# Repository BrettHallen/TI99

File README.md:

# [PSU Replacement](/TI994A_PSU_Replacement)
A fork of a fork.  <br>
Created a version using KiCad 9, with rounded corners and more information to make the build more "idiot proof".<br>

Replaces the 99/4A's original dual-voltage 18VAC/7.5VAC power supply with a regulated 12VDC supply.  The board then generates the required ±5VDC voltages using a DC-DC buck converter (+5VDC) and switching regulator (-5VDC).  The +12VDC comes directly from the external power supply.<br>

## Main Parts
- DFRobot DFR0831 DC-DC Buck Converter (+5VDC supply)
- Recom R-78CK5.0-0.5 Switching Regulator (-5VDC supply)
- Vishay SUP53P06-20 MOSFET (protects against reverse polarity DC input)
- G-Switch SS-22G88-G090 DPDT switch (need to trim a little)

## Original Designs
- [Johnny Blanchard's original](https://codeberg.org/Jonn-reenthused/TI99-4A-dc-power-board)
- [dabone's fork](https://github.com/dabonetn/ti99psu-replacement)

## Status
- 2-Nov-2025: Designed, not yet fabbed & tested, need to double-check switch position

# [Joystick Adaptor](/JoystickAdaptor)
Wanted to design my own joystick adaptor, so I did.

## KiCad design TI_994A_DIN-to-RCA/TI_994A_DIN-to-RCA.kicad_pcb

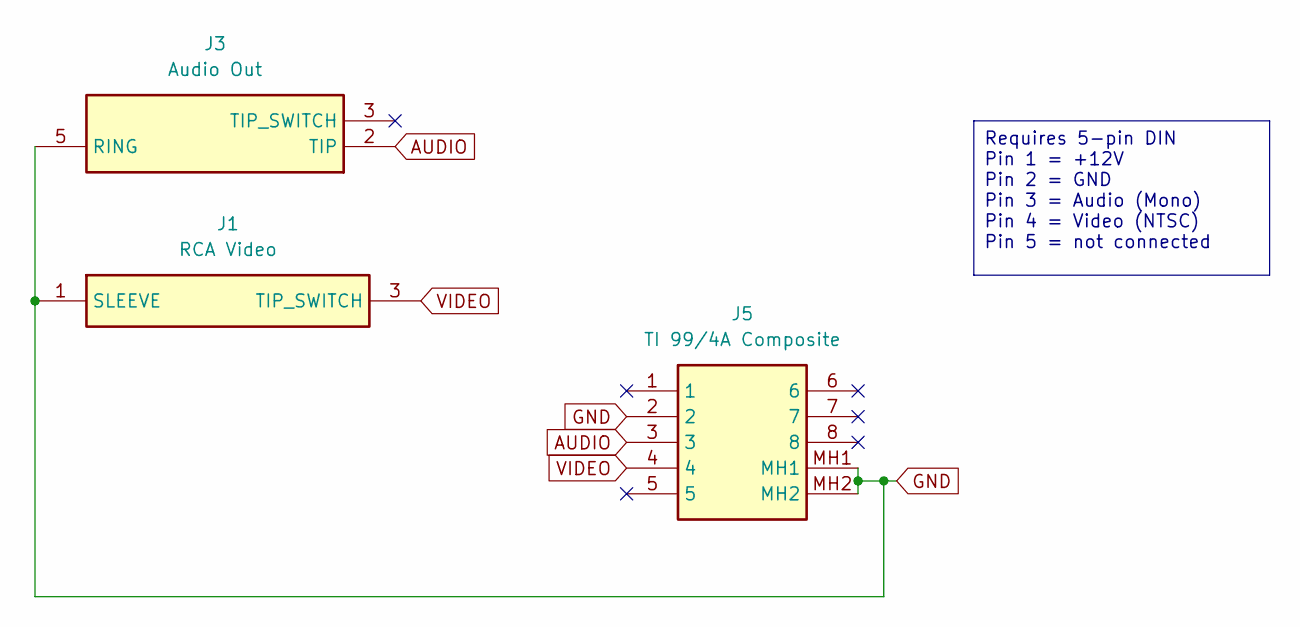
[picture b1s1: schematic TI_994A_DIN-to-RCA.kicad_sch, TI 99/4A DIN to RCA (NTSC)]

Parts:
J1: RCA Video; FC68371; Manufacturer_Part_Number FC68371
J3: Audio Out; SJ3350820BTR; Mouser Part Number 179-SJ3-350820B-TR
J5: TI 99/4A Composite; 6710801; Manufacturer_Part_Number 671-0801

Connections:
AUDIO: J3.2 (TIP), J5.3
GND: J1.1 (SLEEVE), J3.5 (RING), J5.2, J5.MH1, J5.MH2
VIDEO: J1.3 (TIP_SWITCH), J5.4

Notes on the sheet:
Requires 5-pin DIN Pin 1 = +12V Pin 2 = GND Pin 3 = Audio (Mono) Pin 4 = Video (NTSC) Pin 5 = not connected

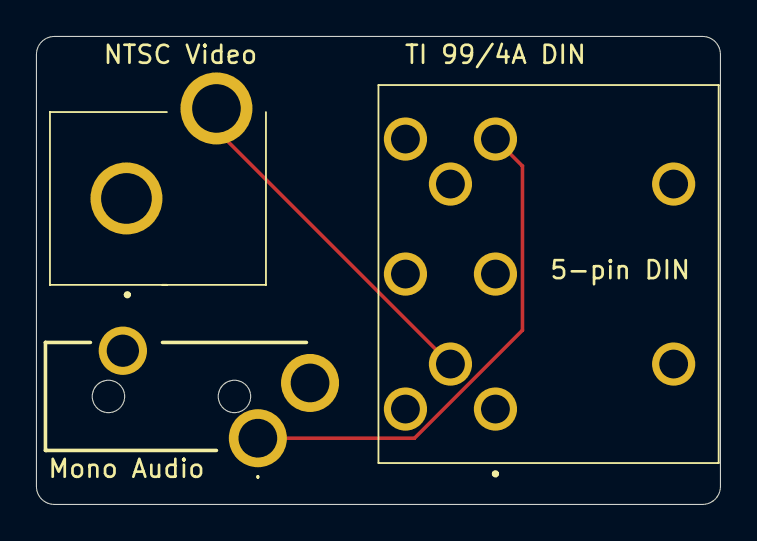
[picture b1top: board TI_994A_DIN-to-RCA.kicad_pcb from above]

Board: 2 copper layers, 38.0 x 26.0 mm, 3 parts (0 on the bottom side), 3 nets.

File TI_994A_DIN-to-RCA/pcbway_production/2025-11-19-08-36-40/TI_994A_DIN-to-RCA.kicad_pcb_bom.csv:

Designator,Quantity,Value,Footprint,Package,MPN,DNP,Mount_Type,Description,Height,Manufacturer_Name,Mouser Part Number,Mouser Price/Stock
J1,1,RCA Video,FC68371,,FC68371,,tht,Socket; RCA; female; angled 90; THT; nickel plated; Marker: black,14,CLIFF ELECTRONIC COMPONENTS,,
J3,1,Audio Out,SJ3350820BTR,,SJ3-350820B-TR,,tht,"3.5 mm Stereo Jack, Through Hole, 2 Conductors, 1 Internal Switches,  Tape & Reel Packaging",5.3,Same Sky,179-SJ3-350820B-TR,https://www.mouser.co.uk/ProductDetail/Same-Sky/SJ3-350820B-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
J5,1,TI 99/4A Composite,6710801,,671-0801,,tht,"Deltron 8 Pole Right Angle Din Socket Socket, 2A, 100 V ac, Lockable",19.5,DELTRON COMPONENTS,,

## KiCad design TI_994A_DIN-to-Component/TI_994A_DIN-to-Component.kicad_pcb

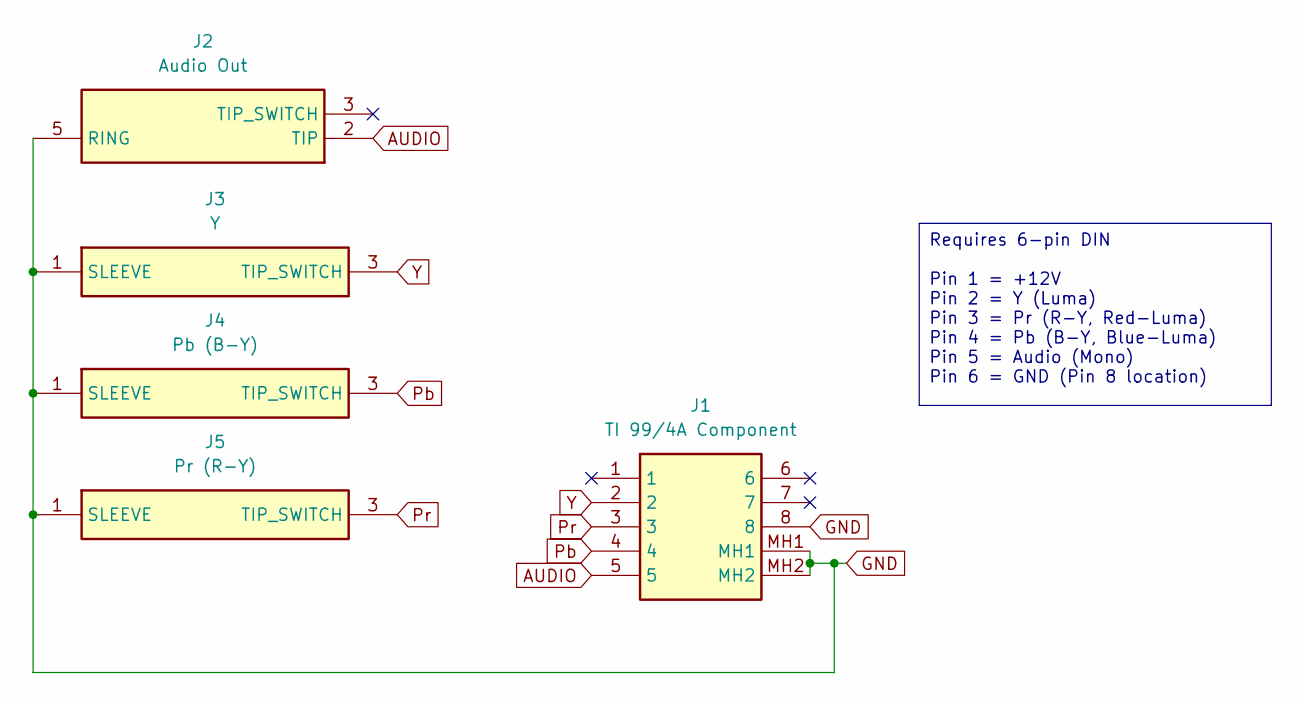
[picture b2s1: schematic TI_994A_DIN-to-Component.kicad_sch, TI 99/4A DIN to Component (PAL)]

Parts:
J1: TI 99/4A Component; 6710801; Manufacturer_Part_Number 671-0801
J2: Audio Out; SJ3350820BTR; Mouser Part Number 179-SJ3-350820B-TR
J3: Y; FC68371; Manufacturer_Part_Number FC68371
J4: Pb (B-Y); FC68371; Manufacturer_Part_Number FC68371
J5: Pr (R-Y); FC68371; Manufacturer_Part_Number FC68371

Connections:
AUDIO: J1.5, J2.2 (TIP)
GND: J1.8, J1.MH1, J1.MH2, J2.5 (RING), J3.1 (SLEEVE), J4.1 (SLEEVE), J5.1 (SLEEVE)
Pb: J1.4, J4.3 (TIP_SWITCH)
Pr: J1.3, J5.3 (TIP_SWITCH)
Y: J1.2, J3.3 (TIP_SWITCH)

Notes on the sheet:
Requires 6-pin DIN Pin 1 = +12V Pin 2 = Y (Luma) Pin 3 = Pr (R-Y, Red-Luma) Pin 4 = Pb (B-Y, Blue-Luma) Pin 5 = Audio (Mono) Pin 6 = GND (Pin 8 location)

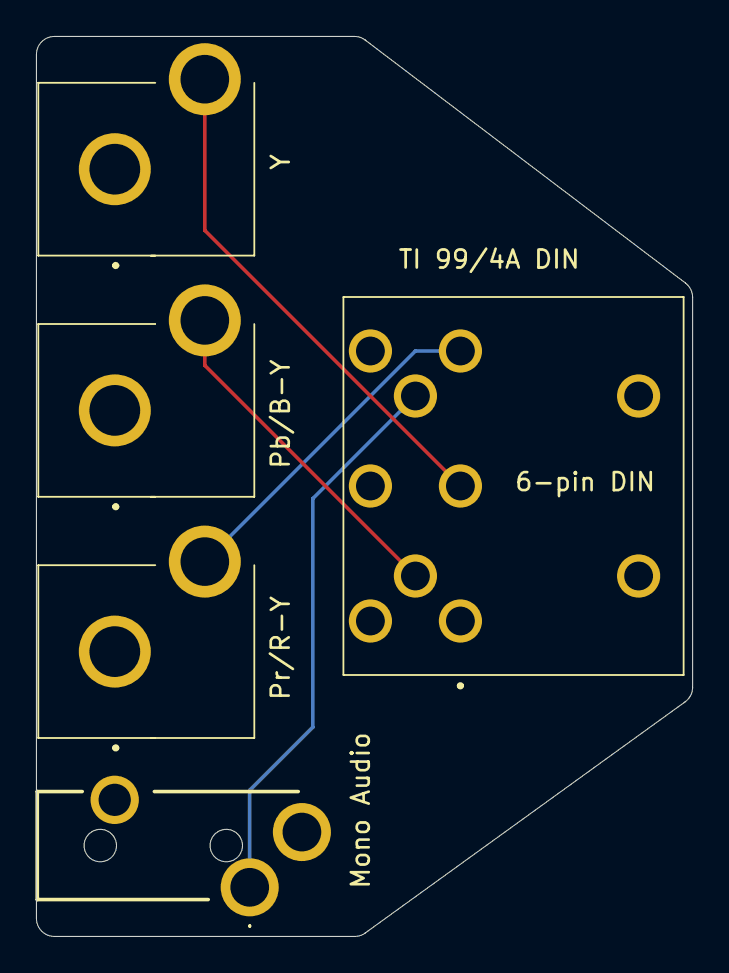
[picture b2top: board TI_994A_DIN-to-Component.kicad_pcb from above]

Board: 2 copper layers, 36.5 x 50.0 mm, 5 parts (0 on the bottom side), 5 nets.

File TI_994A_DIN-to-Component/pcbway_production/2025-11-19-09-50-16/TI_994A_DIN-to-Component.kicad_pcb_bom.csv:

Designator,Quantity,Value,Footprint,Package,MPN,DNP,Mount_Type,Description,Height,Manufacturer_Name,Mouser Part Number,Mouser Price/Stock
J1,1,TI 99/4A Component,6710801,,671-0801,,tht,"Deltron 8 Pole Right Angle Din Socket Socket, 2A, 100 V ac, Lockable",19.5,DELTRON COMPONENTS,,
J2,1,Audio Out,SJ3350820BTR,,SJ3-350820B-TR,,tht,"3.5 mm Stereo Jack, Through Hole, 2 Conductors, 1 Internal Switches,  Tape & Reel Packaging",5.3,Same Sky,179-SJ3-350820B-TR,https://www.mouser.co.uk/ProductDetail/Same-Sky/SJ3-350820B-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
J3,1,Y,FC68371,,FC68371,,tht,Socket; RCA; female; angled 90; THT; nickel plated; Marker: black,14,CLIFF ELECTRONIC COMPONENTS,,
J4,1,Pb (B-Y),FC68371,,FC68371,,tht,Socket; RCA; female; angled 90; THT; nickel plated; Marker: black,14,CLIFF ELECTRONIC COMPONENTS,,
J5,1,Pr (R-Y),FC68371,,FC68371,,tht,Socket; RCA; female; angled 90; THT; nickel plated; Marker: black,14,CLIFF ELECTRONIC COMPONENTS,,

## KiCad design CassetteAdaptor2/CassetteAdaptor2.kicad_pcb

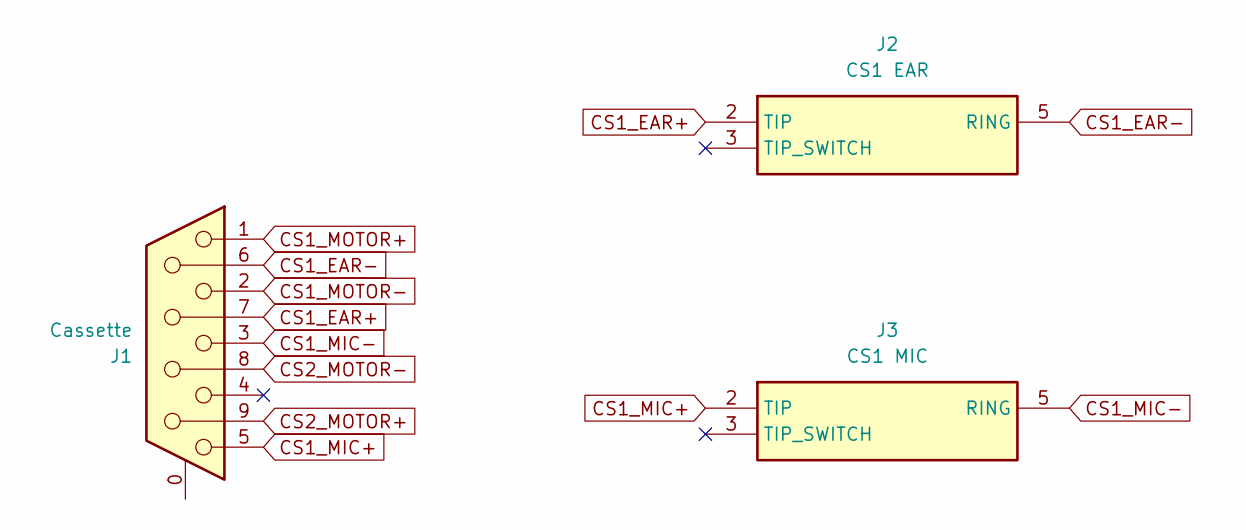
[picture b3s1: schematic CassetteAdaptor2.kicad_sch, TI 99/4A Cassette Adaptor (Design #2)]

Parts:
J1: Cassette; DSUB-9_Pins_EdgeMount_P2.77mm
J2: CS1 EAR; SJ3350820BTR; Mouser Part Number 179-SJ3-350820B-TR
J3: CS1 MIC; SJ3350820BTR; Mouser Part Number 179-SJ3-350820B-TR

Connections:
CS1_EAR+: J1.7, J2.2 (TIP)
CS1_EAR-: J1.6, J2.5 (RING)
CS1_MIC+: J1.5, J3.2 (TIP)
CS1_MIC-: J1.3, J3.5 (RING)
CS1_MOTOR+: J1.1
CS1_MOTOR-: J1.2
CS2_MOTOR+: J1.9
CS2_MOTOR-: J1.8

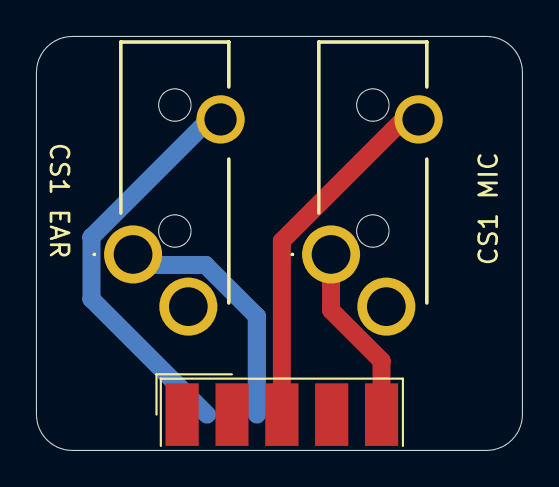
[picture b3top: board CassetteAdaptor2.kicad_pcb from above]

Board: 2 copper layers, 27.0 x 23.0 mm, 3 parts (0 on the bottom side), 4 nets.

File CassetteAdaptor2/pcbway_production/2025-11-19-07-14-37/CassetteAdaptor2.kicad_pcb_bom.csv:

Designator,Quantity,Value,Footprint,Package,MPN,DNP,Mount_Type,Description,Height,Mouser Part Number,Mouser Price/Stock,Manufacturer_Name
J1,1,Cassette,DSUB-9_Pins_EdgeMount_P2.77mm,,,,smt,"9-pin D-SUB connector, socket (female), Mounting Hole",,,,
J2,1,CS1 EAR,SJ3350820BTR,,SJ3-350820B-TR,,tht,"3.5 mm Stereo Jack, Through Hole, 2 Conductors, 1 Internal Switches,  Tape & Reel Packaging",5.3,179-SJ3-350820B-TR,https://www.mouser.co.uk/ProductDetail/Same-Sky/SJ3-350820B-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,Same Sky
J3,1,CS1 MIC,SJ3350820BTR,,SJ3-350820B-TR,,tht,"3.5 mm Stereo Jack, Through Hole, 2 Conductors, 1 Internal Switches,  Tape & Reel Packaging",5.3,179-SJ3-350820B-TR,https://www.mouser.co.uk/ProductDetail/Same-Sky/SJ3-350820B-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,Same Sky

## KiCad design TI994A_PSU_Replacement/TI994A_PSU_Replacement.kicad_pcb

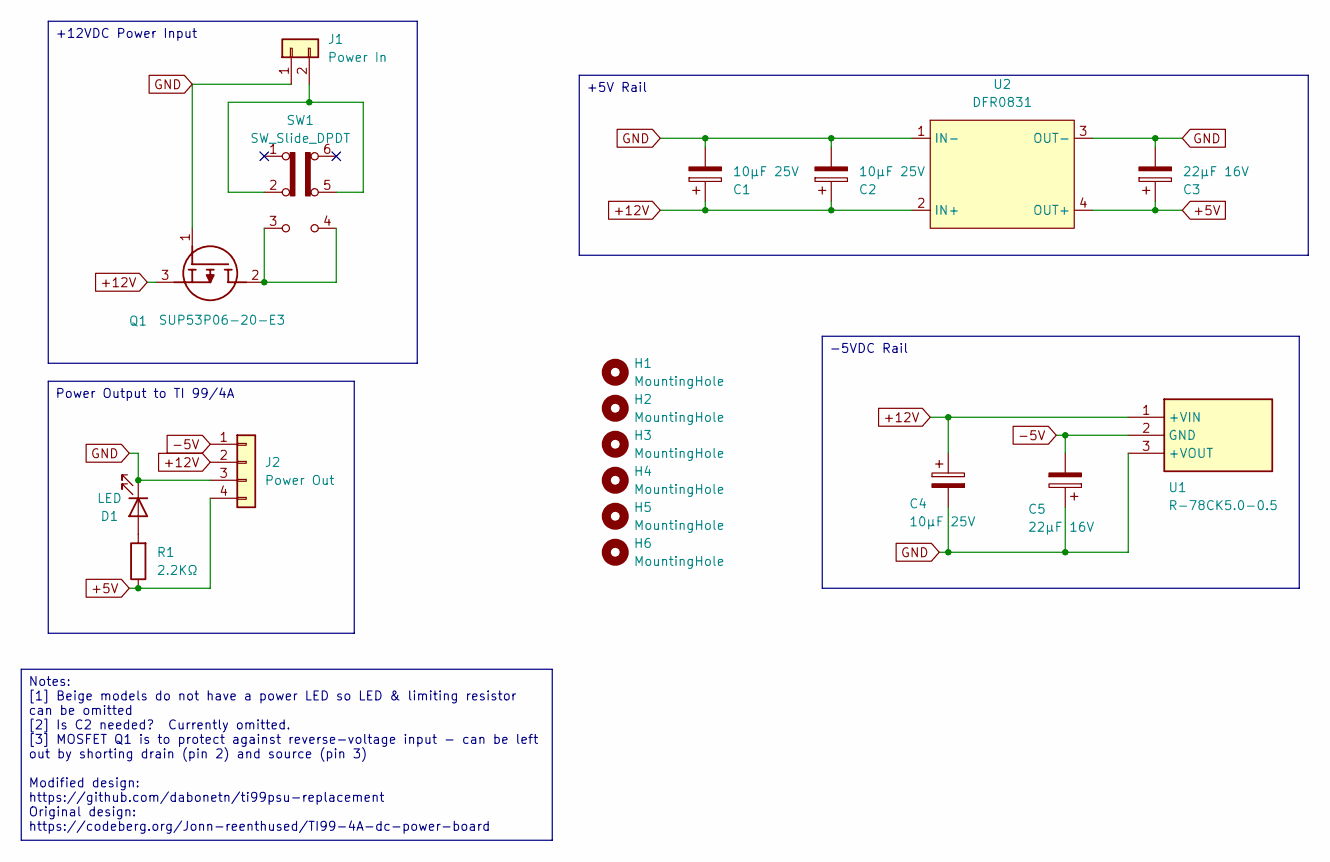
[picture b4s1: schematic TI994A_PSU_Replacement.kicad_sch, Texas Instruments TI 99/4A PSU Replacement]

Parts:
C1, C2, C4: 10µF 25V; C_Radial_D5.0mm_H5.0mm_P2.00mm
C3, C5: 22µF 16V; C_Radial_D5.0mm_H5.0mm_P2.00mm
D1: LED; LED_D5.0mm
H1, H2, H3, H4, H5: MountingHole; MountingHole_4mm
H6: MountingHole; MountingHole_6mm
J1: Power In; JST_VH_B2P-VH_1x02_P3.96mm_Vertical
J2: Power Out; JST_VH_B4P-VH_1x04_P3.96mm_Vertical
Q1: SUP53P06-20-E3; TO254P465X1028X1931-3P; Mouser Part Number 781-SUP53P06-20-E3
R1: 2.2KΩ; R_Axial_DIN0207_L6.3mm_D2.5mm_P7.62mm_Horizontal
SW1: SW_Slide_DPDT; SS-22G88-G090 DPDT
U1: R-78CK5.0-0.5; R78CK5005; Manufacturer_Part_Number R-78CK5.0-0.5
U2: DFR0831

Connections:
+5V: C3.1, J2.4, R1.1, U2.4 (OUT+)
+12V: C1.1, C2.1, C4.1, J2.2, Q1.3 (S), U1.1 (+VIN), U2.2 (IN+)
-5V: C5.2, J2.1, U1.2 (GND)
GND: C1.2, C2.2, C3.2, C4.2, C5.1, D1.1 (K), J1.1, J2.3, Q1.1 (G), U1.3 (+VOUT), U2.1 (IN-), U2.3 (OUT-)
unnamed: D1.2 (A), R1.2
unnamed: J1.2, SW1.2 (B), SW1.5 (B)
unnamed: Q1.2 (D), SW1.3 (C), SW1.4 (A)

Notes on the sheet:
+12VDC Power Input
-5VDC Rail
Power Output to TI 99/4A
Notes: [1] Beige models do not have a power LED so LED & limiting resistor can be omitted [2] Is C2 needed? Currently omitted. [3] MOSFET Q1 is to protect against reverse-voltage input - can be left out by shorting drain (pin 2) and source (pin 3) Modified design: https://github.com/dabonetn/ti99ps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
+5V Rail

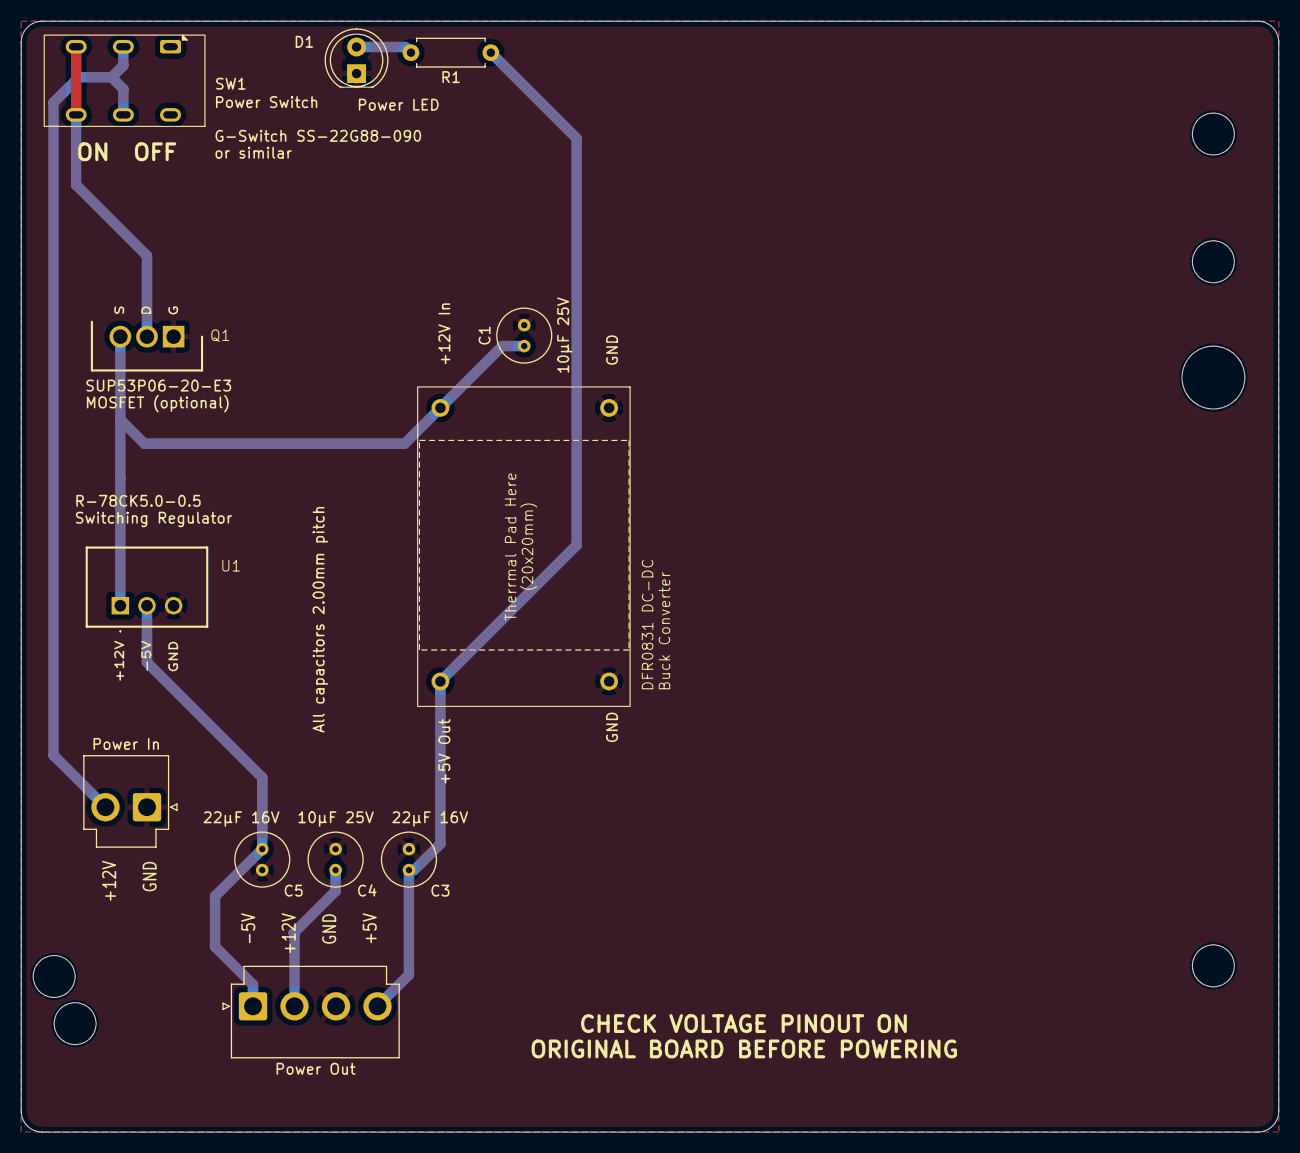
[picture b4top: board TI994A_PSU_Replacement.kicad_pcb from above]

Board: 2 copper layers, 120.0 x 106.0 mm, 18 parts (0 on the bottom side), 7 nets.

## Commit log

2025-11-01 Initial design in KiCad
2025-11-06 Resized 3D images
2025-11-07 Added 3D images
2026-01-21 PCBs fabricated for testing
2026-01-21 Move datasheets to own folder
